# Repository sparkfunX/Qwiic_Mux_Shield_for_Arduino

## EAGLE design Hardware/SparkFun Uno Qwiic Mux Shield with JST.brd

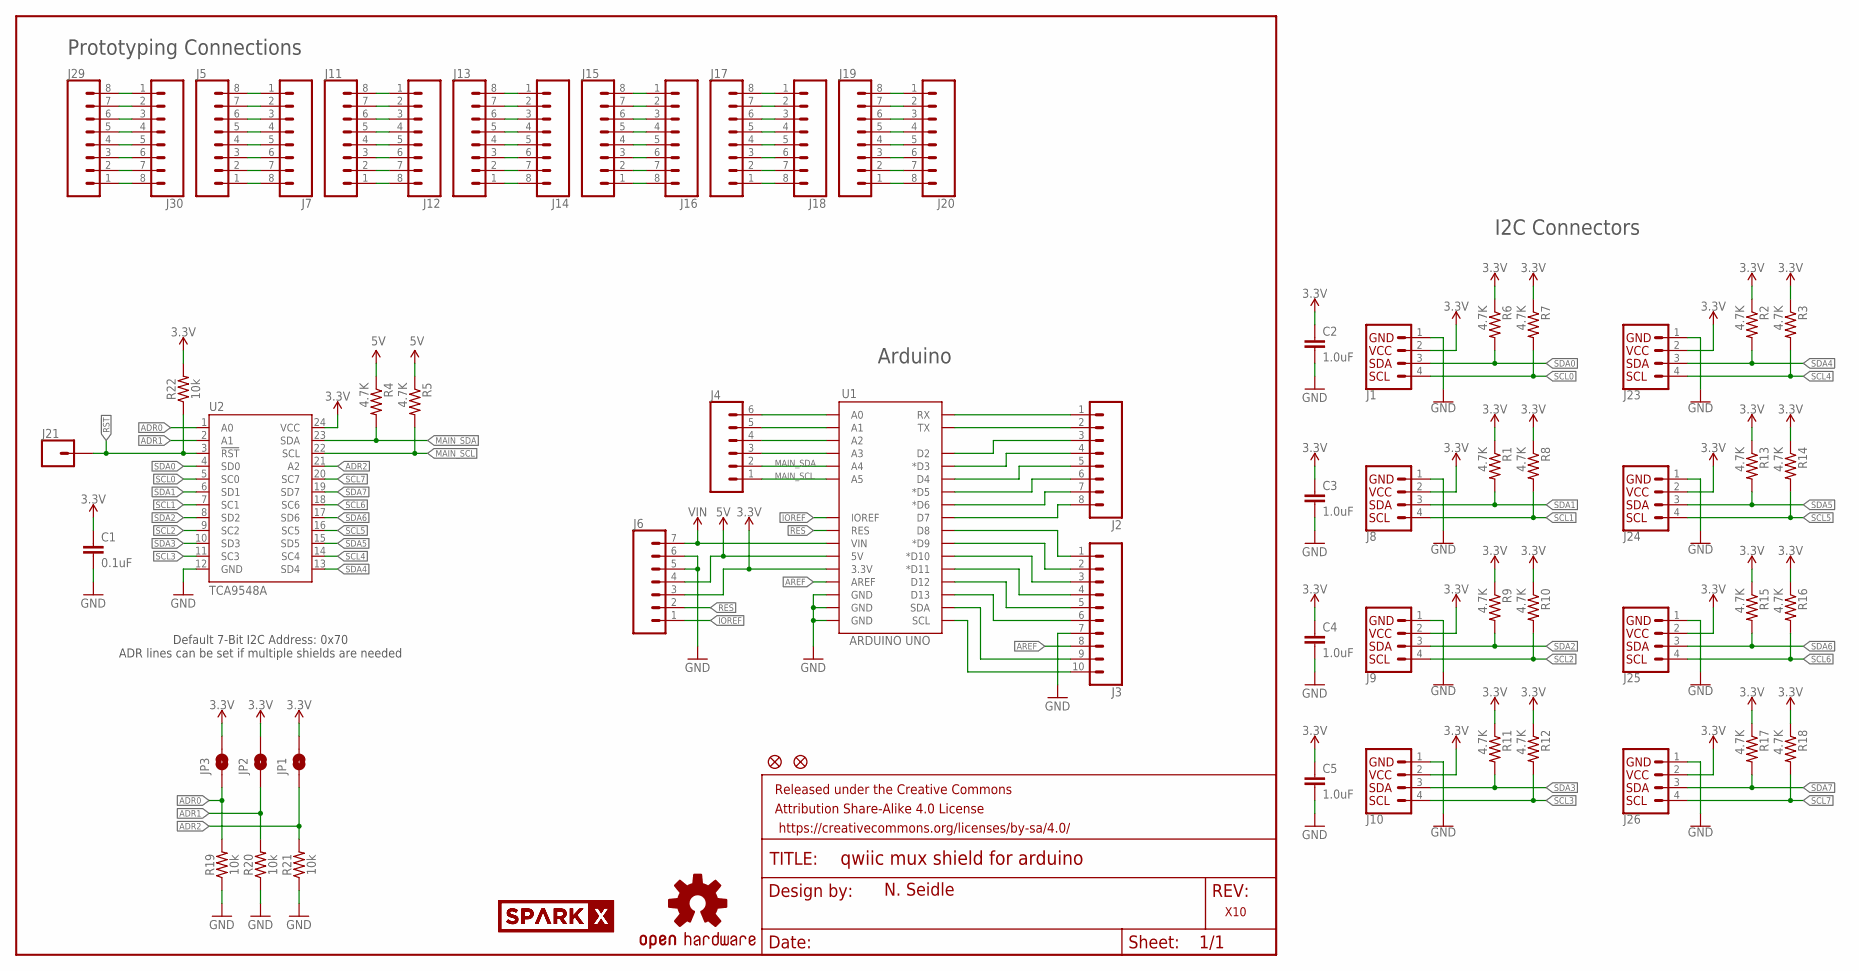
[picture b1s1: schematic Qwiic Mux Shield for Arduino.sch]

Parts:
C1: 0.1uF; 0603
C2, C3, C4, C5: 1.0uF; 0603
FD1, FD2: FIDUCIAL1X2; FIDUCIAL-1X2
FRAME1: FRAME-LETTER; CREATIVE_COMMONS
J1, J8, J9, J10: I2C_STANDARDJS-1MM; 1X04_1MM_RA
J2, J5, J7, J11, J12, J13, J14, J15, J16, J17, J18, J19, J20, J29, J30: CONN_08NO_SILK_FEMALE_PTH; 1X08_NO_SILK
J3: CONN_10NO_SILK_PTH_FEMALE; 1X10_NO_SILK
J4: CONN_06NO_SILK_FEMALE_PTH; 1X06_NO_SILK
J6: CONN_07NO_SILK; 1X07_NO_SILK
J21: CONN_01; 1X01
J23, J24, J25, J26: I2C_STANDARDSILK; 1X04
JP1, JP2, JP3: JUMPER-SMT_2_NO_SILK; SMT-JUMPER_2_NO_SILK
LOGO1: OSHW-LOGOMINI; OSHW-LOGO-MINI
R1, R2, R3, R4, R5, R6, R7, R8, R9, R10, R11, R12, R13, R14, R15, R16, R17, R18: 4.7K; 0603-RES
R19, R20, R21, R22: 10k; 0603
U1: ARDUINO UNO; UNO_R3_SHIELD_NOLABELS
U2: TCA9548A; TSSOP28
U$1: SPARKX-LOGO3; SPARKX-SMALL
U$2: SPARKX-LOGO5; SPARKX-LARGE

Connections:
3.3V: C1.1, C2.1, C3.1, C4.1, C5.1, J1.2 (VCC), J6.3, J8.2 (VCC), J9.2 (VCC), J10.2 (VCC), J23.2 (VCC), J24.2 (VCC), J25.2 (VCC), J26.2 (VCC), JP1.2, JP2.2, JP3.2, R1.1, R2.1, R3.1, R6.1, R7.1, R8.1, R9.1, R10.1, R11.1, R12.1, R13.1, R14.1, R15.1, R16.1, R17.1, R18.1, R22.2, U1.3.3V, U2.24 (VCC)
5V: J6.4, R4.1, R5.1, U1.5V
!RST: J21.1, R22.1, U2.3 (!RST)
A0: J4.6, U1.A0
A1: J4.5, U1.A1
A2: J4.4, U1.A2
A3: J4.3, U1.A3
ADR0: JP3.1, R19.2, U2.1 (A0)
ADR1: JP2.1, R20.2, U2.2 (A1)
ADR2: JP1.1, R21.2, U2.21 (A2)
AREF: J3.8, U1.AREF
D2: J2.3, U1.D2
D3: J2.4, U1.D3 (*D3)
D4: J2.5, U1.D4
D5: J2.6, U1.D5 (*D5)
D6: J2.7, U1.D6 (*D6)
D7: J2.8, U1.D7
D8: J3.1, U1.D8
D9: J3.2, U1.D9 (*D9)
D10: J3.3, U1.D10 (*D10)
D11: J3.4, U1.D11 (*D11)
D12: J3.5, U1.D12
D13: J3.6, U1.D13
GND: C1.2, C2.2, C3.2, C4.2, C5.2, J1.1 (GND), J3.7, J6.5, J6.6, J8.1 (GND), J9.1 (GND), J10.1 (GND), J23.1 (GND), J24.1 (GND), J25.1 (GND), J26.1 (GND), R19.1, R20.1, R21.1, U1.GND@0 (GND), U1.GND@1 (GND), U1.GND@2 (GND), U2.12 (GND)
IOREF: J6.1, U1.IOREF
MAIN_SCL: J4.1, R5.2, U1.A5, U2.22 (SCL)
MAIN_SCL_1: J3.10, U1.SCL
MAIN_SDA: J4.2, R4.2, U1.A4, U2.23 (SDA)
MAIN_SDA_1: J3.9, U1.SDA
unnamed: J5.8, J7.1
unnamed: J5.7, J7.2
unnamed: J5.6, J7.3
unnamed: J5.5, J7.4
unnamed: J5.4, J7.5
unnamed: J5.3, J7.6
unnamed: J5.2, J7.7
unnamed: J5.1, J7.8
unnamed: J11.8, J12.1
unnamed: J11.7, J12.2
unnamed: J11.6, J12.3
unnamed: J11.5, J12.4
unnamed: J11.4, J12.5
unnamed: J11.3, J12.6
unnamed: J11.2, J12.7
unnamed: J11.1, J12.8
unnamed: J13.8, J14.1
unnamed: J13.7, J14.2
unnamed: J13.6, J14.3
unnamed: J13.5, J14.4
unnamed: J13.4, J14.5
unnamed: J13.3, J14.6
unnamed: J13.2, J14.7
unnamed: J13.1, J14.8
unnamed: J15.8, J16.1
unnamed: J15.7, J16.2
unnamed: J15.6, J16.3
unnamed: J15.5, J16.4
unnamed: J15.4, J16.5
unnamed: J15.3, J16.6
unnamed: J15.2, J16.7
unnamed: J15.1, J16.8
unnamed: J17.8, J18.1
unnamed: J17.7, J18.2
unnamed: J17.6, J18.3
unnamed: J17.5, J18.4
unnamed: J17.4, J18.5
unnamed: J17.3, J18.6
unnamed: J17.2, J18.7
unnamed: J17.1, J18.8
unnamed: J19.8, J20.1
unnamed: J19.7, J20.2
unnamed: J19.6, J20.3
unnamed: J19.5, J20.4
unnamed: J19.4, J20.5
unnamed: J19.3, J20.6
unnamed: J19.2, J20.7
unnamed: J19.1, J20.8
unnamed: J29.8, J30.1
unnamed: J29.7, J30.2
unnamed: J29.6, J30.3
unnamed: J29.5, J30.4
unnamed: J29.4, J30.5
unnamed: J29.3, J30.6
unnamed: J29.2, J30.7
unnamed: J29.1, J30.8
RES: J6.2, U1.RES
RX: J2.1, U1.RX
SCL0: J1.4 (SCL), R7.2, U2.5 (SC0)
SCL1: J8.4 (SCL), R8.2, U2.7 (SC1)
SCL2: J9.4 (SCL), R10.2, U2.9 (SC2)
SCL3: J10.4 (SCL), R12.2, U2.11 (SC3)
SCL4: J23.4 (SCL), R3.2, U2.14 (SC4)
SCL5: J24.4 (SCL), R14.2, U2.16 (SC5)
SCL6: J25.4 (SCL), R16.2, U2.18 (SC6)
SCL7: J26.4 (SCL), R18.2, U2.20 (SC7)
SDA0: J1.3 (SDA), R6.2, U2.4 (SD0)
SDA1: J8.3 (SDA), R1.2, U2.6 (SD1)
SDA2: J9.3 (SDA), R9.2, U2.8 (SD2)
SDA3: J10.3 (SDA), R11.2, U2.10 (SD3)
SDA4: J23.3 (SDA), R2.2, U2.13 (SD4)
SDA5: J24.3 (SDA), R13.2, U2.15 (SD5)
SDA6: J25.3 (SDA), R15.2, U2.17 (SD6)
SDA7: J26.3 (SDA), R17.2, U2.19 (SD7)
TX: J2.2, U1.TX
VIN: J6.7, U1.VIN

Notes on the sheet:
N. Seidle
Arduino
X10
Prototyping Connections
I2C Connectors
Default 7-Bit I2C Address: 0x70 ADR lines can be set if multiple shields are needed

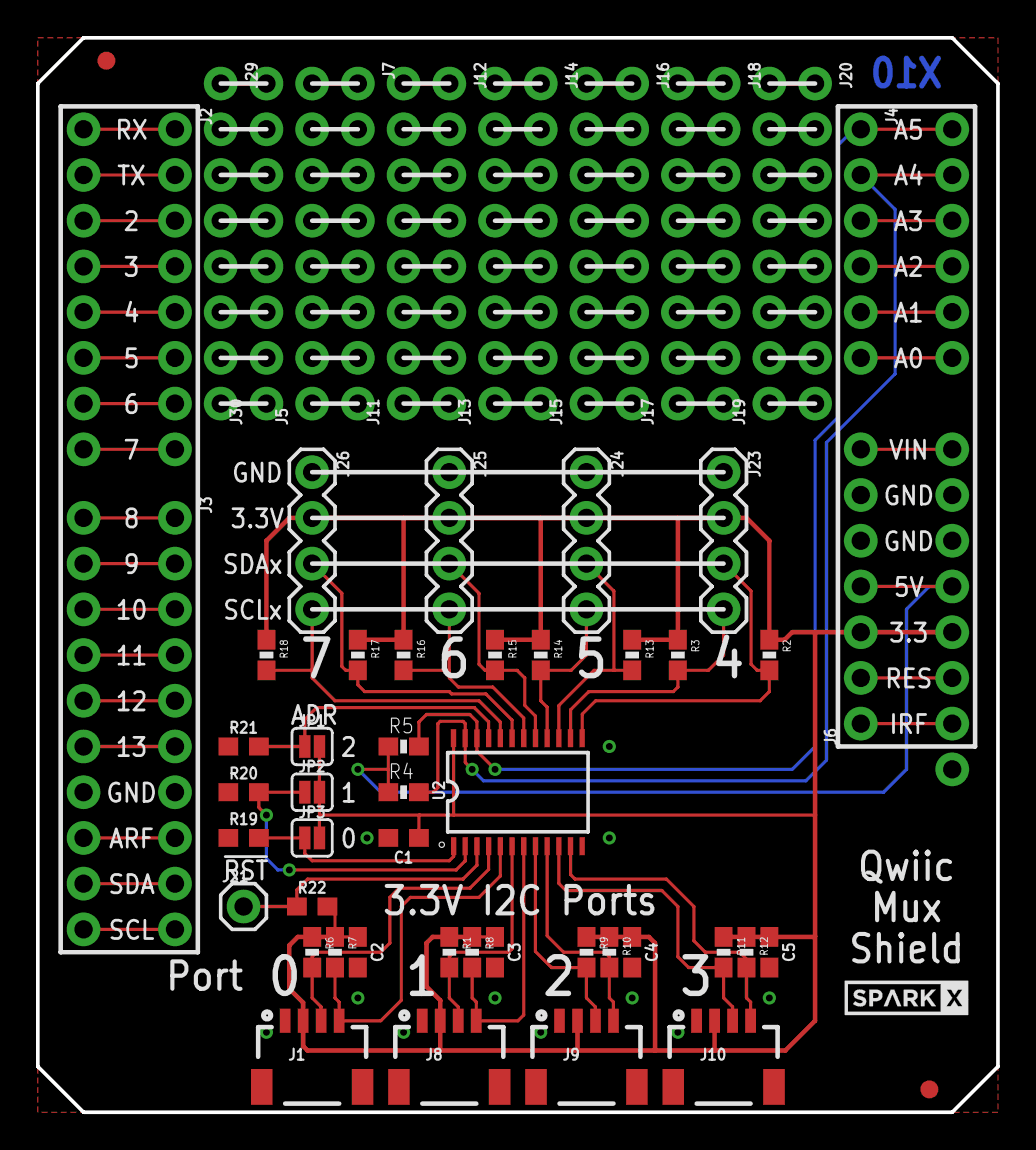
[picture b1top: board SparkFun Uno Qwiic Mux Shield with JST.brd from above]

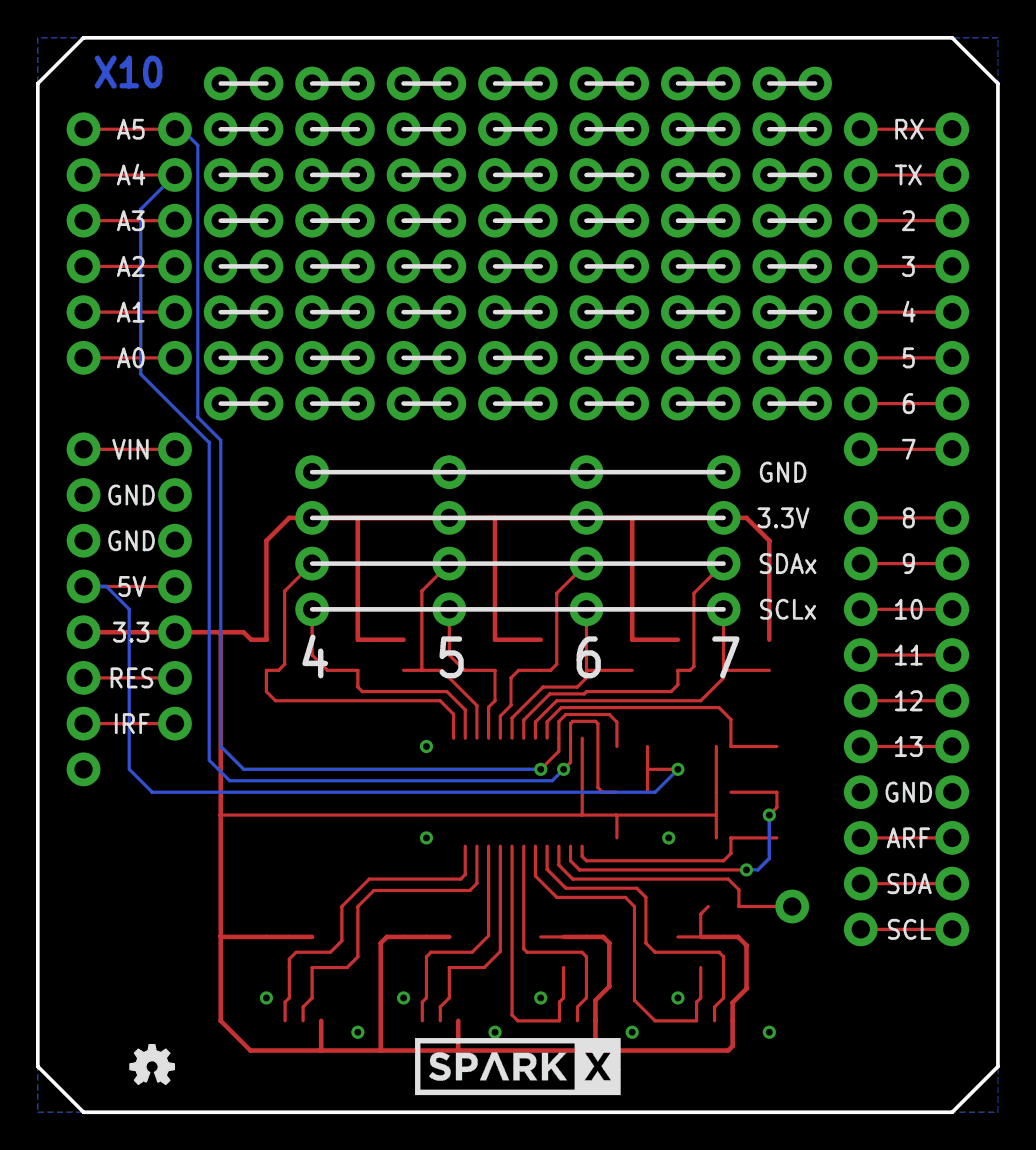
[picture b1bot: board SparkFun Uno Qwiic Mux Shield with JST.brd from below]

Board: 2 copper layers, 53.3 x 59.7 mm, 65 parts (2 on the bottom side), 105 nets.

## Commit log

2017-04-02 :circus_tent: Added .gitattributes & .gitignore files
2017-04-05 Adding comments to example

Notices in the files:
parts and their libraries:
SparkFun-Boards: Licensing: CC v3.0 Share-Alike You are welcome to use this library for commercial purposes.
SparkFun-Aesthetics: Released under the Creative Commons Attribution Share-Alike 4.0 License
SparkFun-Aesthetics: https://creativecommons.org/licenses/by-sa/4.0
